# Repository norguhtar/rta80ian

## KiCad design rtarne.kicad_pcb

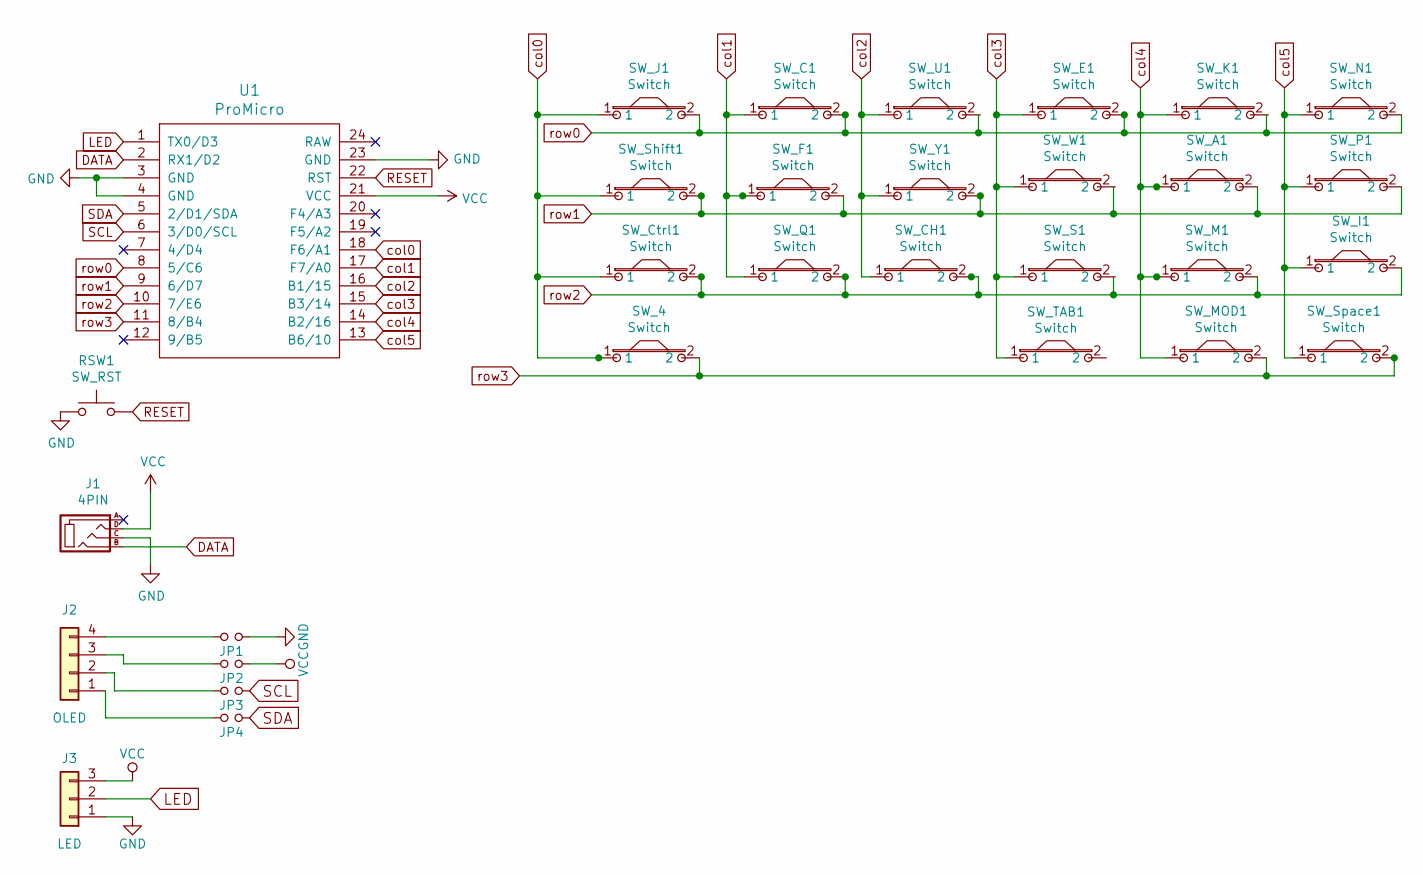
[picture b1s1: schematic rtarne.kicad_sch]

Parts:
J1: 4PIN; MJ-4PP-9_1side
J2: OLED
J3: LED; StripLED_rev
JP1, JP2, JP3, JP4: Jumper
RSW1: SW_RST; ResetSW_1side
SW_4: Switch; SW_RTA80
SW_A1: Switch; SW_RTA80
SW_C1: Switch; SW_RTA80
SW_CH1: Switch; SW_RTA80
SW_Ctrl1: Switch; SW_RTA80
SW_E1: Switch; SW_RTA80
SW_F1: Switch; SW_RTA80
SW_I1: Switch; SW_RTA80
SW_J1: Switch; SW_RTA80
SW_K1: Switch; SW_RTA80
SW_M1: Switch; SW_RTA80
SW_MOD1: Switch; SW_RTA80
SW_N1: Switch; SW_RTA80
SW_P1: Switch; SW_RTA80
SW_Q1: Switch; SW_RTA80
SW_S1: Switch; SW_RTA80
SW_Shift1: Switch; SW_RTA80
SW_Space1: Switch; SW_RTA80
SW_TAB1: Switch; SW_RTA80
SW_U1: Switch; SW_RTA80
SW_W1: Switch; SW_RTA80
SW_Y1: Switch; SW_RTA80
U1: ProMicro; ProMicro_v3

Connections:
DATA: J1.B, U1.2 (RX1/D2)
GND: J1.C, J3.1, JP1.1, RSW1.1, U1.3 (GND), U1.4 (GND), U1.23 (GND)
LED: J3.2, U1.1 (TX0/D3)
unnamed: J2.1, JP4.2
unnamed: J2.2, JP3.2
unnamed: J2.3, JP2.2
unnamed: J2.4, JP1.2
RESET: RSW1.2, U1.22 (RST)
SCL: JP3.1, U1.6 (3/D0/SCL)
SDA: JP4.1, U1.5 (2/D1/SDA)
VCC: J1.D, J3.3, JP2.1, U1.21 (VCC)
col0: SW_4.1, SW_Ctrl1.1, SW_J1.1, SW_Shift1.1, U1.18 (F6/A1)
col1: SW_C1.1, SW_F1.1, SW_Q1.1, U1.17 (F7/A0)
col2: SW_CH1.1, SW_U1.1, SW_Y1.1, U1.16 (B1/15)
col3: SW_E1.1, SW_S1.1, SW_TAB1.1, SW_W1.1, U1.15 (B3/14)
col4: SW_A1.1, SW_K1.1, SW_M1.1, SW_MOD1.1, U1.14 (B2/16)
col5: SW_I1.1, SW_N1.1, SW_P1.1, SW_Space1.1, U1.13 (B6/10)
row0: SW_C1.2, SW_E1.2, SW_J1.2, SW_N1.2, U1.8 (5/C6)
row1: SW_A1.2, SW_F1.2, SW_P1.2, SW_Shift1.2, SW_Y1.2, U1.9 (6/D7)
row2: SW_CH1.2, SW_Ctrl1.2, SW_I1.2, SW_M1.2, SW_Q1.2, U1.10 (7/E6)
row3: SW_4.2, SW_MOD1.2, SW_Space1.2, U1.11 (8/B4)

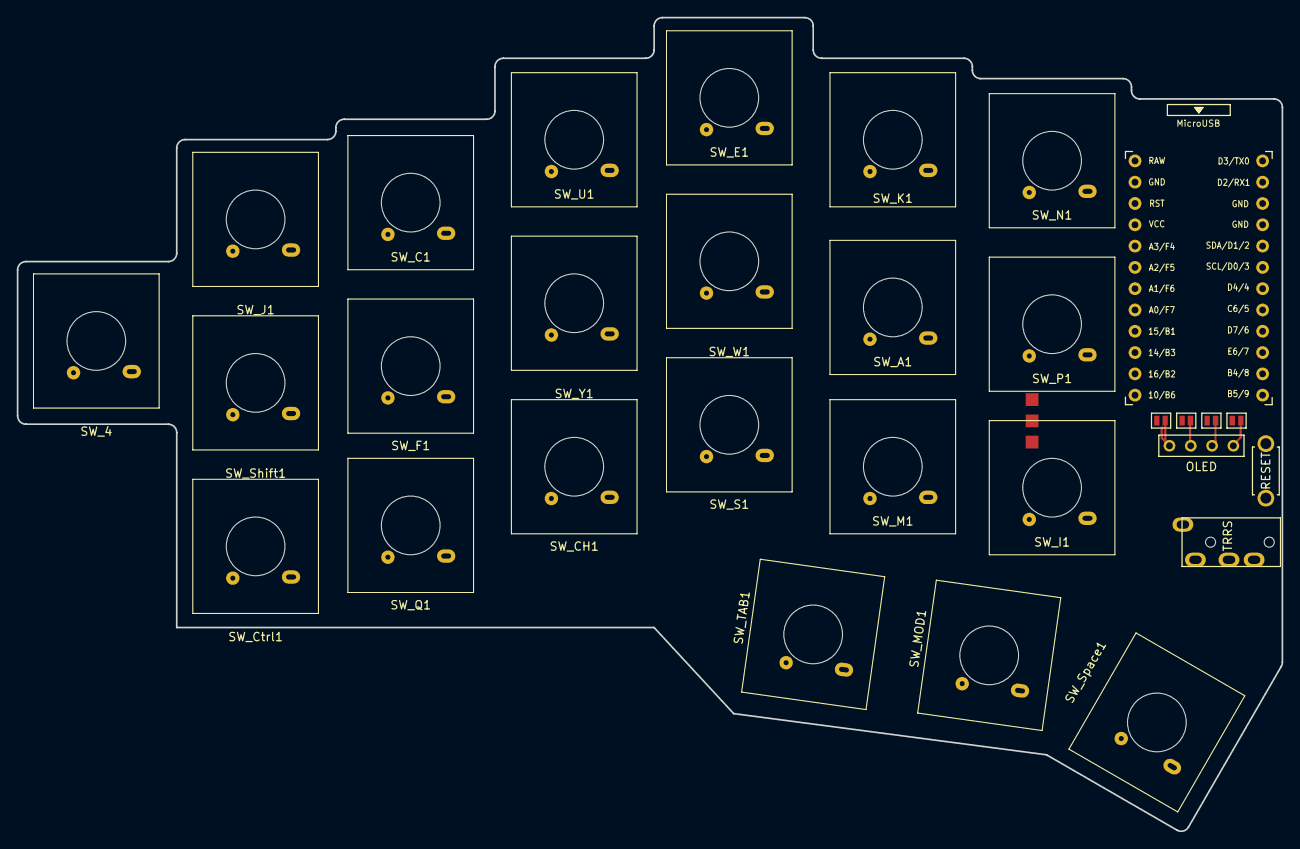
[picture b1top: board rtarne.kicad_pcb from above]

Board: 2 copper layers, 150.9 x 97.1 mm, 31 parts (0 on the bottom side), 21 nets.

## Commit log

2021-01-11 Ad kbd submodule. Add promicro to circut
2021-01-23 Add switch footprint
2021-01-24 Update footprint
2021-01-25 Add switches in electric schema
2021-01-27 Recreate schema
2021-01-28 Add PCB elements. Update pin and add connect pin from footprint
2021-02-20 Add edge cut and set switch case plase
